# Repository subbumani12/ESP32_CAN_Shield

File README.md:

# ESP32 CAN Shield

A compact ESP32 expansion shield designed to provide reliable and protected CAN bus communication for automotive and industrial applications. The shield integrates a high-speed CAN transceiver, automotive input protection, onboard buck converter, status LEDs, and an ESP32-compatible header for seamless CAN interfacing using the ESP32's built-in TWAI (CAN) controller.

---

## Overview

This project implements a custom ESP32 CAN Shield intended for applications requiring robust communication over Controller Area Network (CAN). The board accepts an automotive battery input, converts it to a regulated 3.3 V supply, interfaces directly with an ESP32 development board, and provides protection against common automotive electrical transients.

The hardware has been designed in KiCad with emphasis on simplicity, reliability, and ease of integration with ESP32-based embedded systems.

---

## 3D Render

---

## Features

- ESP32 compatible shield interface
- SN65HVD230 3.3 V CAN transceiver
- Native support for ESP32 TWAI (CAN) peripheral
- Wide input automotive power stage
- TPS5435A synchronous buck converter
- CAN bus termination resistor (120 Ω)
- CANH/CANL ESD & surge protection
- Reverse polarity / over-voltage protection using Zener protection stage
- Automotive fuse protection
- Dual status LEDs
- Compact two-layer PCB
- Designed using KiCad

---

## Hardware Architecture

```
Vehicle Battery (12–24 V)
          │
          ▼
 Input Protection
 (Fuse + Zener)
          │
          ▼
 TPS5435A Buck Converter
        3.3 V
          │
          ├──────────────► ESP32 Header
          │
          ▼
 SN65HVD230 CAN Transceiver
          │
   CANH / CANL
          │
 Vehicle CAN Bus
```

---

## Functional Blocks

### 1. Automotive Power Input

The shield accepts an external automotive battery input through the CAN connector.

Protection circuitry includes:

- 500 mA fuse
- 24 V Zener diode
- Input decoupling capacitors

These components protect the downstream electronics from accidental over-voltage conditions and transient disturbances commonly present in automotive environments.

---

### 2. Buck Converter

The board uses the **TPS5435ADDAR** switching regulator to generate a regulated **3.3 V** rail from the vehicle supply.

Main components include:

- Input filtering capacitors
- Bootstrap capacitor
- External inductor
- Output filter capacitors
- Feedback resistor divider
- Compensation network

Advantages of using a switching regulator:

- High efficiency
- Low heat generation
- Suitable for battery-powered systems
- Wide input voltage range

---

### 3. CAN Transceiver

The communication interface is built around the **SN65HVD230**, a 3.3 V high-speed CAN transceiver.

Features:

- Fully compatible with ISO 11898 CAN
- Direct interface with ESP32 TWAI controller
- Differential CANH/CANL outputs
- Low-power standby capability
- High noise immunity

The ESP32 handles all CAN protocol processing internally while the transceiver performs physical layer conversion.

---

### 4. CAN Protection

The CAN interface includes:

- TVS/Zener protection diode
- 120 Ω termination resistor

These components improve robustness against electrical transients and provide proper CAN bus termination when required.

---

### 5. ESP32 Interface

A dual-row connector exposes the required GPIOs for an ESP32 development board.

The interface provides:

- 3.3 V supply
- Ground
- CAN TX
- CAN RX
- User GPIOs
- Status LED connections

The shield is intended to work directly with the ESP32's built-in TWAI peripheral without requiring an external CAN controller.

---

### 6. Status LEDs

Two onboard LEDs are provided for visual indication.

Possible uses include:

- Power indication
- CAN activity
- Firmware status
- Error indication

LED functionality can be configured in software.

---

## Schematic

The hardware consists of five major blocks:

- Step-Down Buck Converter
- CAN Bus Transceiver
- CANH/CANL Protection
- ESP32 Connector
- Status LEDs

---

## PCB Design

Designed in **KiCad**

Design considerations:

- Two-layer PCB
- Short CAN differential routing
- Dedicated ground plane
- Proper decoupling capacitor placement
- Switching regulator layout optimized for reduced noise
- Compact shield form factor

---

## Applications

- Automotive diagnostics
- OBD-II interfaces
- CAN data logging
- Industrial automation
- Motor control
- Robotics
- Electric vehicles
- Battery Management Systems
- ECU communication
- CAN protocol learning

---

## Future Improvements

- CAN-FD support
- Galvanic isolation
- Reverse polarity MOSFET protection
- Common-mode choke on CAN lines
- Screw terminal CAN connector
- OBD-II connector support
- Power LED and CAN TX/RX LEDs
- Onboard programming interface

---

## Tools Used

- KiCad
- ESP32
- TWAI (ESP32 CAN Controller)

---

## License

This project is open-source and intended for educational and research purposes.

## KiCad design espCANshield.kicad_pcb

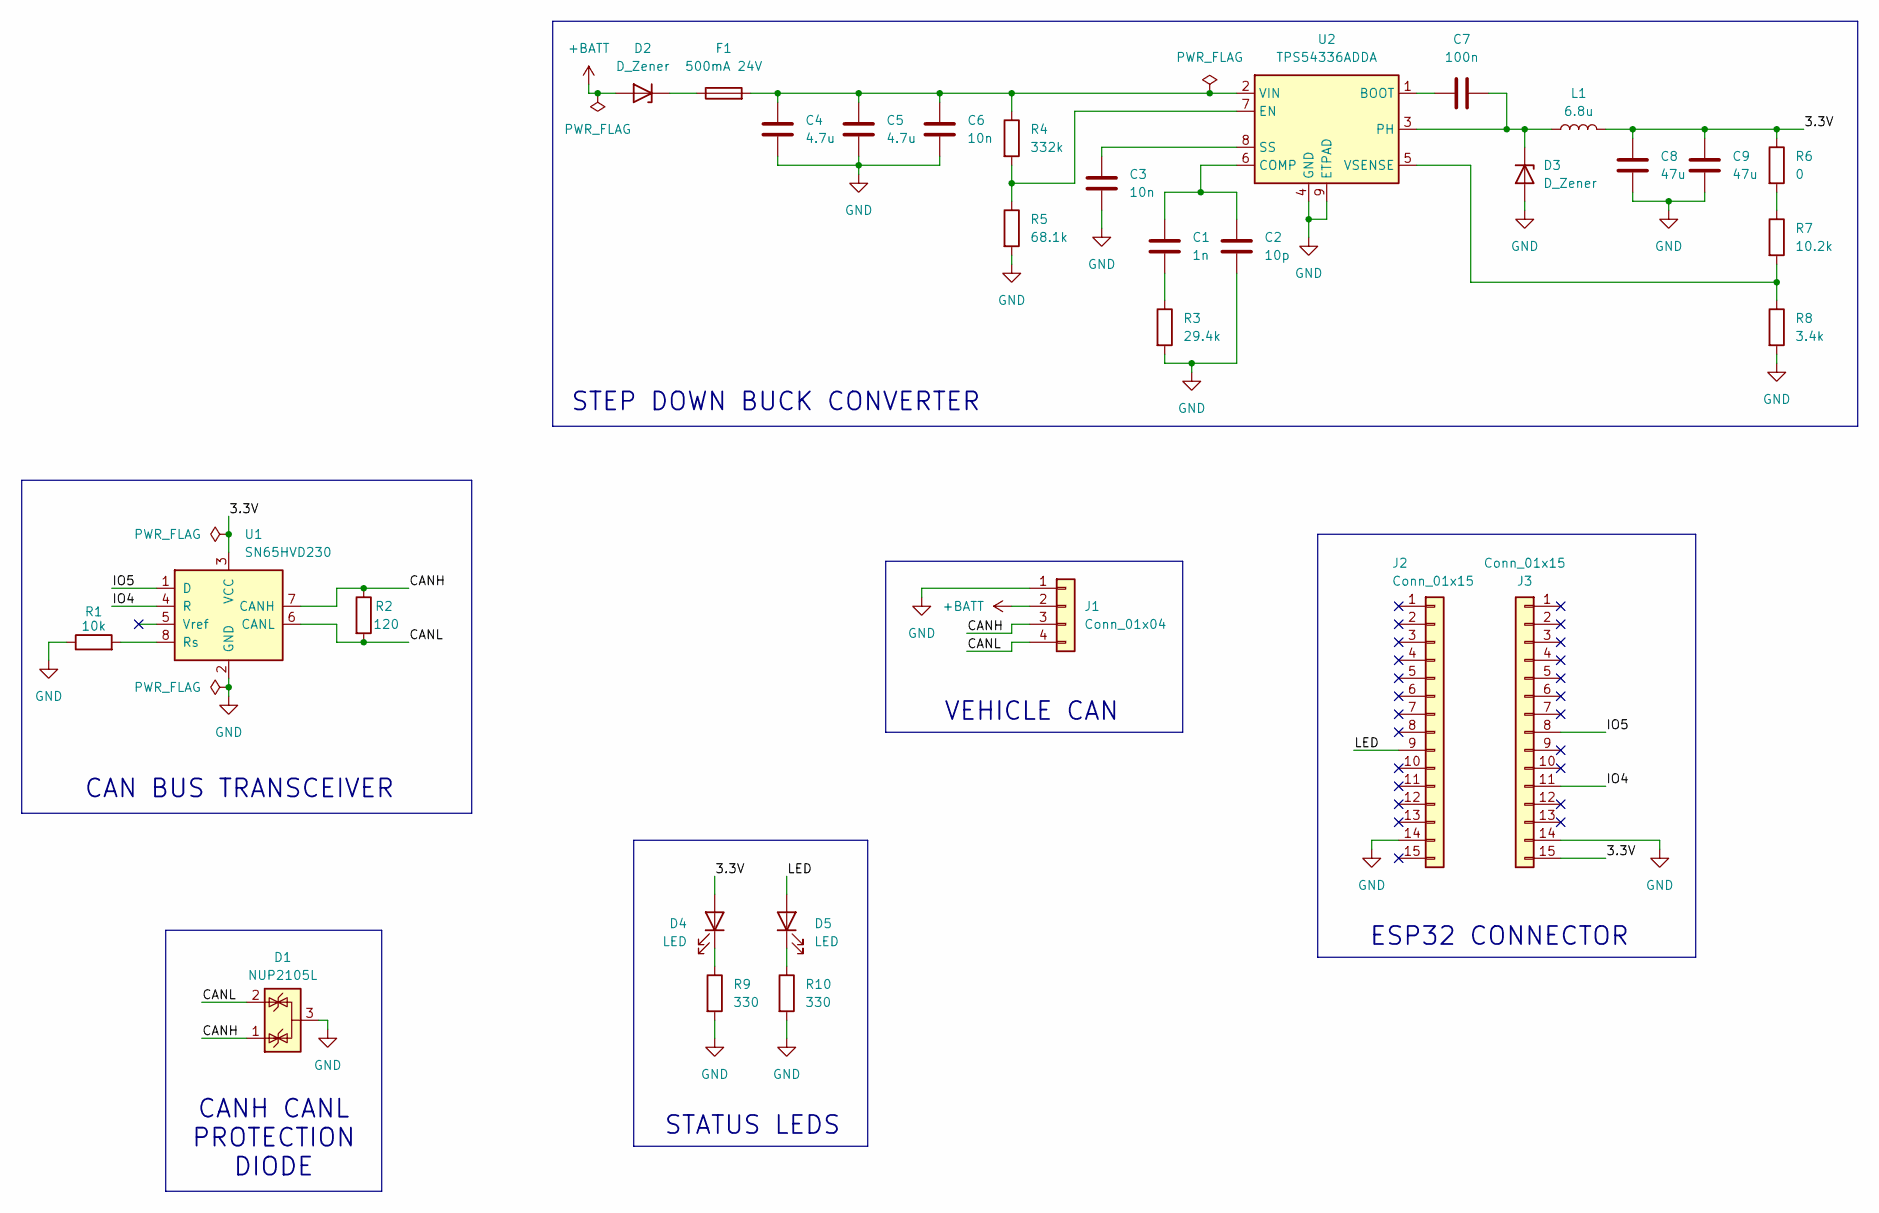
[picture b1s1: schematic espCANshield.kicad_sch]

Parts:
C1: 1n; C_0603_1608Metric
C2: 10p; C_0603_1608Metric
C3, C6: 10n; C_0603_1608Metric
C4, C5: 4.7u; C_0603_1608Metric
C7: 100n; C_0603_1608Metric
C8, C9: 47u; C_0603_1608Metric
D1: NUP2105L; SOT-23
D2, D3: D_Zener; D_0805_2012Metric
D4, D5: LED; LED_1206_3216Metric
F1: 500mA 24V; Fuse_1206_3216Metric
J1: Conn_01x04; PinHeader_1x04_P2.54mm_Vertical
J2, J3: Conn_01x15; PinSocket_1x15_P2.54mm_Vertical
L1: 6.8u; L_0603_1608Metric
R1: 10k; R_0603_1608Metric
R2: 120; R_0603_1608Metric
R3: 29.4k; R_0603_1608Metric
R4: 332k; R_0603_1608Metric
R5: 68.1k; R_0603_1608Metric
R6: 0; R_0603_1608Metric
R7: 10.2k; R_0603_1608Metric
R8: 3.4k; R_0603_1608Metric
R9, R10: 330; R_0603_1608Metric
U1: SN65HVD230; SOIC-8_3.9x4.9mm_P1.27mm
U2: TPS54336ADDA; SOIC-8-1EP_3.9x4.9mm_P1.27mm_EP2.29x3mm

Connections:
+BATT: D2.2 (A), J1.2
/3.3V: C8.1, C9.1, D4.2 (A), J3.15, L1.2, R6.1, U1.3 (VCC)
/CANH: D1.1 (K), J1.3, R2.1, U1.7 (CANH)
/CANL: D1.2 (K), J1.4, R2.2, U1.6 (CANL)
/IO4: J3.11, U1.4 (R)
/IO5: J3.8, U1.1 (D)
/LED: D5.2 (A), J2.9
GND: C2.2, C3.2, C4.2, C5.2, C6.2, C8.2, C9.2, D1.3 (A), D3.2 (A), J1.1, J2.14, J3.14, R1.1, R3.2, R5.2, R8.2, R9.2, R10.2, U1.2 (GND), U2.4 (GND), U2.9 (ETPAD)
unnamed: C1.2, R3.1
unnamed: D2.1 (K), F1.1
unnamed: C7.2, D3.1 (K), L1.1, U2.3 (PH)
unnamed: D4.1 (K), R9.1
unnamed: D5.1 (K), R10.1
unnamed: R6.2, R7.1
unnamed: R1.2, U1.8 (Rs)
unnamed: C7.1, U2.1 (BOOT)
unnamed: C1.1, C2.1, U2.6 (COMP)
unnamed: R4.2, R5.1, U2.7 (EN)
unnamed: C3.1, U2.8 (SS)
unnamed: C4.1, C5.1, C6.1, F1.2, R4.1, U2.2 (VIN)
unnamed: R7.2, R8.1, U2.5 (VSENSE)

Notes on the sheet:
VEHICLE CAN
ESP32 CONNECTOR
STATUS LEDS
CANH CANL PROTECTION DIODE
CAN BUS TRANSCEIVER
STEP DOWN BUCK CONVERTER

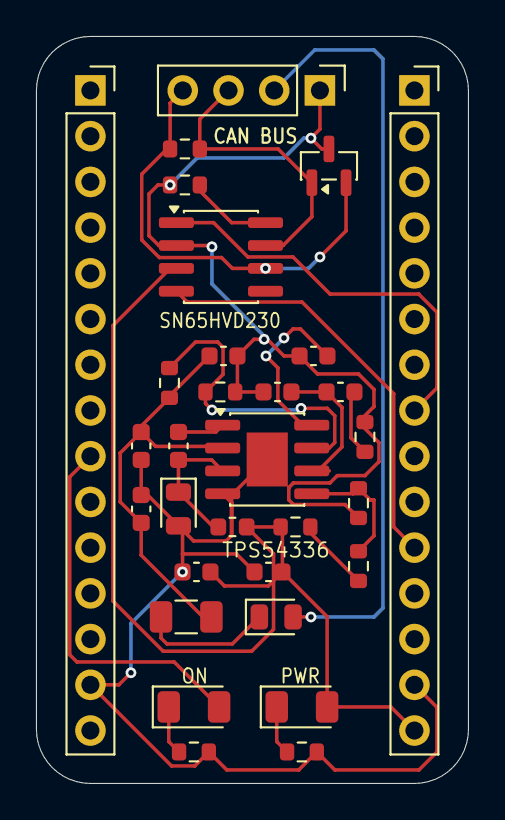
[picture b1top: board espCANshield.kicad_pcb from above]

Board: 2 copper layers, 24.0 x 41.5 mm, 31 parts (0 on the bottom side), 21 nets.
